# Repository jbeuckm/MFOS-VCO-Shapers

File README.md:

# MFOS-VCO-Shapers
http://www.musicfromouterspace.com/analogsynth_new/VCO20120618REV0/VCO20120618REV0.html

This is an add-on board for the MFOS VCO Core that implements the pulse/tri/sine waveform sections of Ray's design.

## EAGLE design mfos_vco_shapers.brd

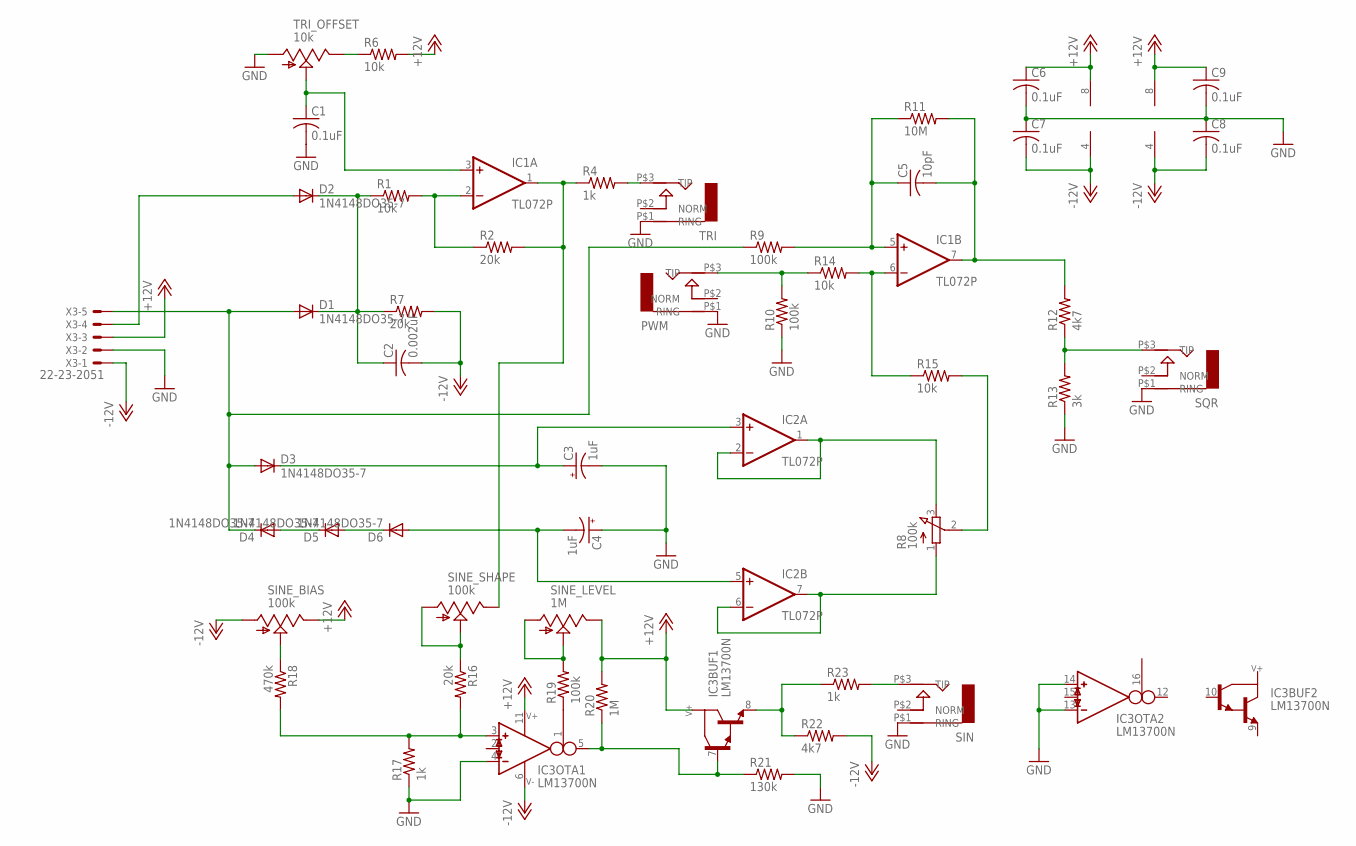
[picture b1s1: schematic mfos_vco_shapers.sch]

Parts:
C1, C6, C7, C8, C9: 0.1uF; C050-030X075
C2: 0.002uF; C050-030X075
C3, C4: 1uF; B45181B
C5: 10pF; C050-024X044
D1, D2, D3, D4, D5, D6: 1N4148DO35-7; DO35-7
IC1, IC2: TL072P; DIL08
IC3: LM13700N; DIL16
PWM: AUDIO-JACK; ERTHENVAR-JACK-90DEG
R1, R6, R14, R15: 10k; 0207/7
R2, R7, R16: 20k; 0207/7
R4, R17, R23: 1k; 0207/7
R8: 100k; 3RP/1610N
R9, R10, R19: 100k; 0207/7
R11: 10M; 0207/7
R12, R22: 4k7; 0207/7
R13: 3k; 0207/7
R18: 470k; 0207/7
R20: 1M; 0207/7
R21: 130k; 0207/7
SIN: AUDIO-JACK; ERTHENVAR-JACK-90DEG
SINE_BIAS: 100k; B64Y
SINE_LEVEL: 1M; B64Y
SINE_SHAPE: 100k; B64Y
SQR: AUDIO-JACK; ERTHENVAR-JACK-90DEG
TRI: AUDIO-JACK; ERTHENVAR-JACK-90DEG
TRI_OFFSET: 10k; B64Y
X3: 22-23-2051

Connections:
+12V: C6.1, C9.1, IC1.8 (V+), IC2.8 (V+), IC3.11 (V+), R6.2, R20.2, SINE_BIAS.E, SINE_LEVEL.E, X3.3
-12V: C2.2, C7.2, C8.2, IC1.4 (V-), IC2.4 (V-), IC3.6 (V-), R7.2, R22.2, SINE_BIAS.A, X3.1
GND: C1.2, C3.-, C4.+, C6.2, C7.1, C8.1, C9.2, IC3.4 (IN_N), IC3.13 (IN_N), IC3.14 (IN_P), PWM.P$1 (RING), R10.1, R13.1, R17.1, R21.2, SIN.P$1 (RING), SQR.P$1 (RING), TRI.P$1 (RING), TRI_OFFSET.A, X3.2
unnamed: D4.A, D5.C
unnamed: D5.A, D6.C
unnamed: C2.1, D1.C, D2.C, R1.1, R7.1
unnamed: IC1.2 (-IN), R1.2, R2.1
unnamed: IC1.1 (OUT), R2.2, R4.1, SINE_SHAPE.E
unnamed: R4.2, TRI.P$3 (TIP)
unnamed: R6.1, TRI_OFFSET.E
unnamed: C1.1, IC1.3 (+IN), TRI_OFFSET.S
unnamed: C4.-, D6.A, IC2.5 (+IN)
unnamed: C3.+, D3.C, IC2.3 (+IN)
unnamed: IC2.1 (OUT), IC2.2 (-IN), R8.3 (E)
unnamed: IC2.6 (-IN), IC2.7 (OUT), R8.1 (A)
unnamed: PWM.P$3 (TIP), R10.2, R14.1
unnamed: C5.1, IC1.5 (+IN), R9.2, R11.1
unnamed: IC1.6 (-IN), R14.2, R15.1
unnamed: C5.2, IC1.7 (OUT), R11.2, R12.2
unnamed: R8.2 (S), R15.2
unnamed: R12.1, R13.2, SQR.P$3 (TIP)
unnamed: IC3.3 (IN_P), R16.2, R17.2, R18.2
unnamed: R16.1, SINE_SHAPE.A, SINE_SHAPE.S
unnamed: R18.1, SINE_BIAS.S
unnamed: R23.2, SIN.P$3 (TIP)
unnamed: IC3.1 (I_BIAS), R19.1
unnamed: R19.2, SINE_LEVEL.A, SINE_LEVEL.S
unnamed: IC3.8 (E), R22.1, R23.1
unnamed: IC3.5 (OUT), IC3.7 (B), R20.1, R21.1
unnamed: D2.A, X3.4
unnamed: D1.A, D3.A, D4.C, R9.1, X3.5

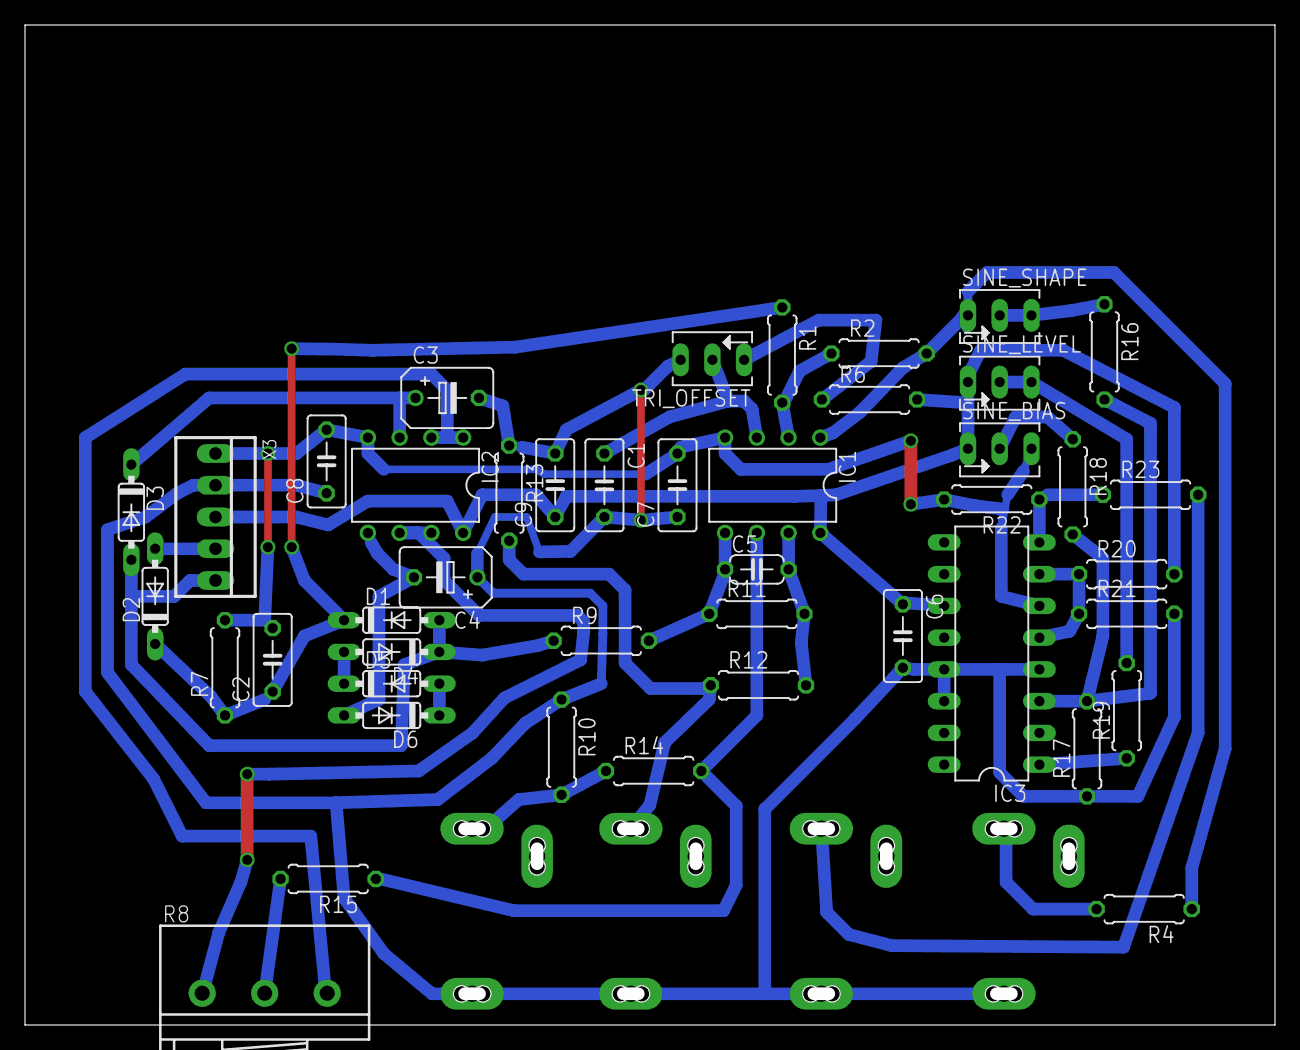
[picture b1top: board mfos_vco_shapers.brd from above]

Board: 2 copper layers, 99.0 x 79.0 mm, 48 parts (0 on the bottom side), 31 nets.

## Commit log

2015-10-02 better spacing and polarized caps
2015-11-29 panel for the two-part vco core and shapers
2016-03-27 fewer jumpers and thicker traces
2016-03-27 layout tweaks
2016-03-27 tweak
